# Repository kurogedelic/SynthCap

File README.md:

# SynthCap

A MIDI / CV interface "Cap" for the M5Stack CardputerZero. It plugs into the EXT 2.54-14P header. Designed in KiCad 10.

| Front (encoders) | Back (jacks and SMD parts) |
|---|---|
|  |  |

**Status: work in progress.** The board has been auto-routed but never built. Nothing here is tested on hardware.

## Features
- MCU: CH32V303CBT6, connected to the CardputerZero as a USB MIDI device (EXT pins 1 and 3)
- MIDI IN / OUT on 3.5mm TRS (Type A)
- 2 x CV out (0-5V, internal DAC + LMV324) and 2 x Gate out
- Clock in / out
- 4 x rotary encoder with push switch (Alps EC12E)
- 80 x 32mm, 2 layers. All SMD parts are on the back, for single-side assembly at JLCPCB
- Firmware upload is meant to work from the CardputerZero alone, over the chip's USB ISP bootloader (`wchisp`)

## Schematic
[Schematic (PDF)](docs/schematic.pdf)

## Folders
| Path | Contents |
|---|---|
| `SynthCap.kicad_*` | KiCad project |
| `SynthCap.pretty/`, `SynthCap.3dshapes/` | Project footprints and 3D models |
| `tools/` | Scripts that generate the schematic, footprints and board. `tools/design.py` is the single source for the circuit |
| `jlcpcb/` | BOM and CPL for JLCPCB assembly |
| `shell/` | 3D-printed shell (OpenSCAD) |
| `docs/` | Schematic and renders |
| `memos/` | Design notes (Japanese) |

## Not included
- The PJ-342 jack datasheet (LCSC part C668606). The footprint was drawn from its land pattern drawing.
- The Alps EC11E STEP model. To see the encoders in the 3D viewer, put `EC11E-05SW.STEP` in `SynthCap.3dshapes/`.

## Known open points
- The Tip / Ring pin mapping of the PJ-342 jack is read from the drawing and not confirmed on a real part.
- The encoder footprint uses SMD pads for a through-hole part (legs are bent or cut and soldered on the surface).
- The position of the mounting ear holes against the CardputerZero screw points is estimated from drawings.

## Warning
`tools/gen_pcb.py` rebuilds the board from scratch and removes all routing. Do not run it on a routed board.

## License
Copyright (c) 2026 kurogedelic

- Hardware design, shell and documentation (everything outside `tools/`): [CC BY-SA 4.0](LICENSE)
- Scripts in `tools/`: [MIT](tools/LICENSE)

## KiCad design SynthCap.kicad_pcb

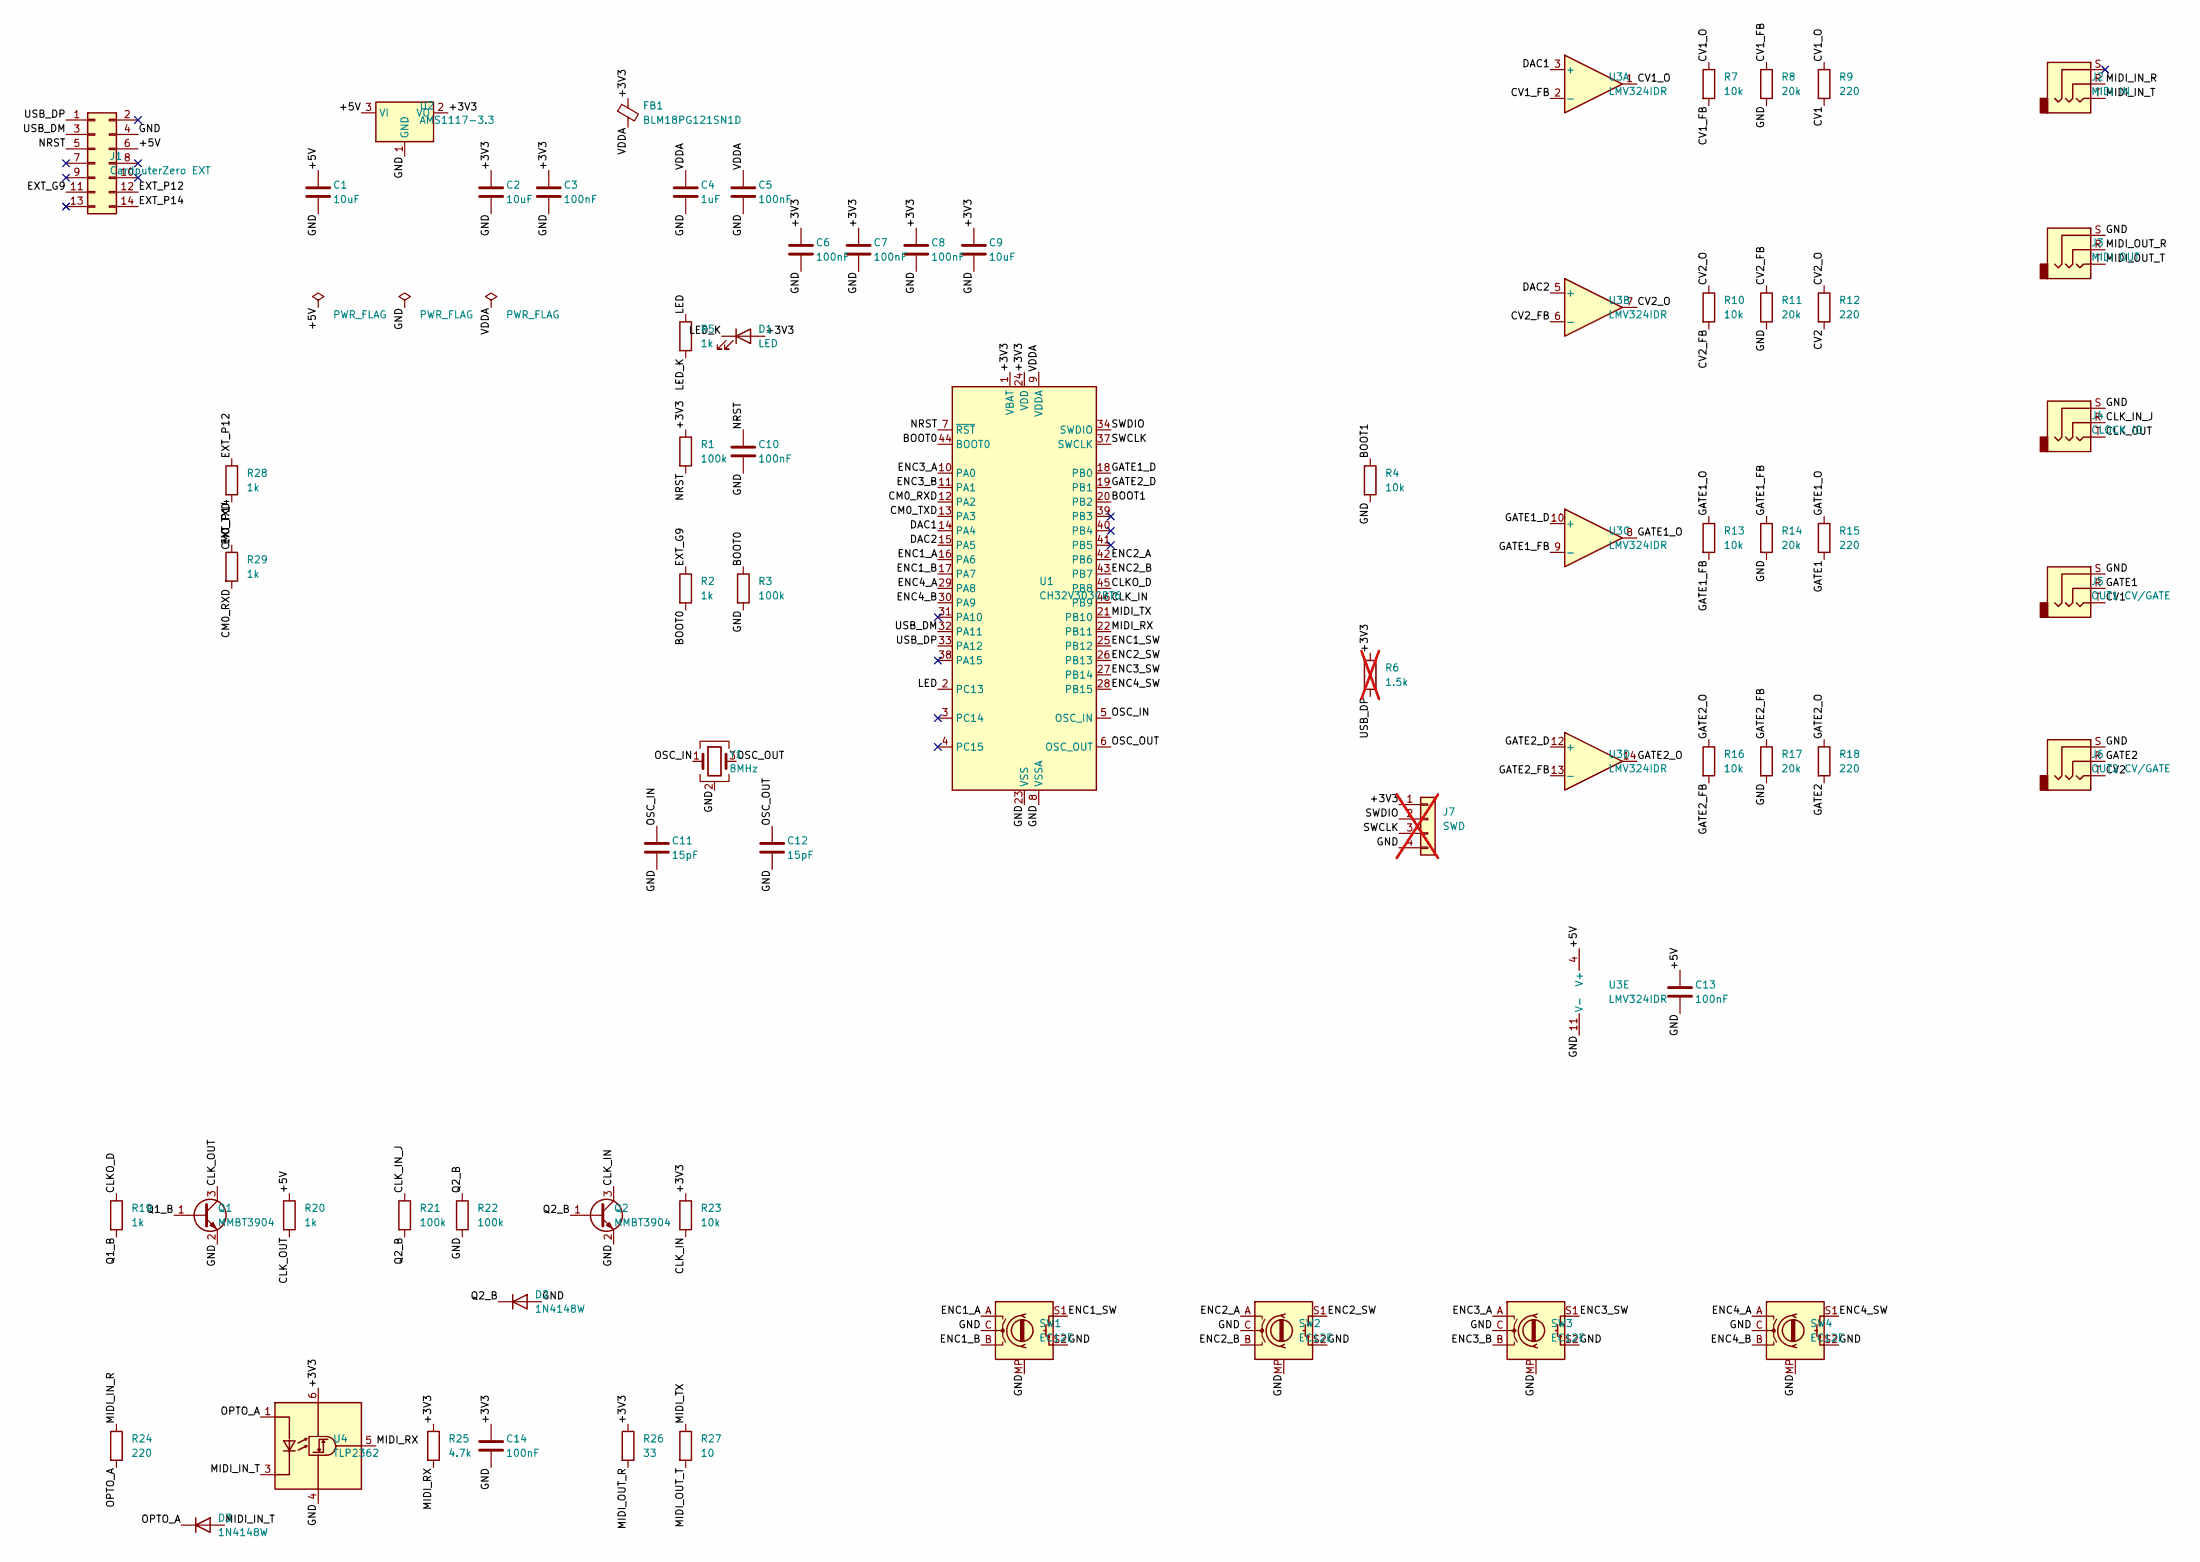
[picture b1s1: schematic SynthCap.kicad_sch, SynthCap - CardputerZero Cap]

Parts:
C1, C2, C9: 10uF; C_0805_2012Metric; LCSC C15850
C3, C5, C6, C7, C8, C10, C13, C14: 100nF; C_0603_1608Metric; LCSC C14663
C4: 1uF; C_0603_1608Metric; LCSC C15849
C11, C12: 15pF; C_0603_1608Metric; LCSC C1644
D1: LED; LED_0603_1608Metric; LCSC C2286
D2, D3: 1N4148W; D_SOD-123; LCSC C81598
FB1: BLM18PG121SN1D; L_0603_1608Metric; LCSC C14709
J1: CardputerZero EXT; PinHeader_2x07_P2.54mm_Horizontal
J2: MIDI IN; Jack_3.5mm_SHOUHAN_PJ-342_SMD; LCSC C668606
J3: MIDI OUT; Jack_3.5mm_SHOUHAN_PJ-342_SMD; LCSC C668606
J4: CLOCK IO; Jack_3.5mm_SHOUHAN_PJ-342_SMD; LCSC C668606
J5: OUT1 CV/GATE; Jack_3.5mm_SHOUHAN_PJ-342_SMD; LCSC C668606
J6: OUT2 CV/GATE; Jack_3.5mm_SHOUHAN_PJ-342_SMD; LCSC C668606
J7: SWD; PinHeader_1x04_P1.27mm_Vertical; not fitted
Q1, Q2: MMBT3904; SOT-23; LCSC C20526
R1, R3, R21, R22: 100k; R_0603_1608Metric; LCSC C25803
R2, R5, R19, R20, R28, R29: 1k; R_0603_1608Metric; LCSC C21190
R4, R7, R10, R13, R16, R23: 10k; R_0603_1608Metric; LCSC C25804
R6: 1.5k; R_0603_1608Metric; LCSC C22843; not fitted
R8, R11, R14, R17: 20k; R_0603_1608Metric; LCSC C4184
R9, R12, R15, R18, R24: 220; R_0603_1608Metric; LCSC C22962
R25: 4.7k; R_0603_1608Metric; LCSC C23162
R26: 33; R_0603_1608Metric; LCSC C23140
R27: 10; R_0603_1608Metric; LCSC C22859
SW1, SW2, SW3, SW4: EC12E; RotaryEncoder_Alps_EC12E-Switch_Vertical_H20mm_SMDpads
U1: CH32V303CBT6; LQFP-48_7x7mm_P0.5mm; LCSC C7494374
U2: AMS1117-3.3; SOT-223-3_TabPin2; LCSC C6186
U3: LMV324IDR; SOIC-14_3.9x8.7mm_P1.27mm; LCSC C7974
U4: TLP2362; SO-5-6_4.55x3.7mm_P1.27mm; LCSC C37658
Y1: 8MHz; Crystal_SMD_3225-4Pin_3.2x2.5mm; LCSC C367183

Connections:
/+3V3: C2.1, C3.1, C6.1, C7.1, C8.1, C9.1, C14.1, D1.2 (A), FB1.1, J7.1, R1.1, R6.1, R23.1, R25.1, R26.1, U1.1 (VBAT), U1.24 (VDD), U1.36 (VDD), U1.48 (VDD), U2.2 (VO), U4.6 (VDD)
/+5V: C1.1, C13.1, J1.6, R20.1, U2.3 (VI), U3.4 (V+)
/BOOT0: R2.2, R3.1, U1.44 (BOOT0)
/BOOT1: R4.1, U1.20 (PB2)
/CLKO_D: R19.1, U1.45 (PB8)
/CLK_IN: Q2.3 (C), R23.2, U1.46 (PB9)
/CLK_IN_J: J4.R, R21.1
/CLK_OUT: J4.T, Q1.3 (C), R20.2
/CM0_RXD: R29.2, U1.12 (PA2)
/CM0_TXD: R28.2, U1.13 (PA3)
/CV1: J5.T, R9.2
/CV1_FB: R7.2, R8.1, U3.2 (-)
/CV1_O: R7.1, R9.1, U3.1
/CV2: J6.T, R12.2
/CV2_FB: R10.2, R11.1, U3.6 (-)
/CV2_O: R10.1, R12.1, U3.7
/DAC1: U1.14 (PA4), U3.3 (+)
/DAC2: U1.15 (PA5), U3.5 (+)
/ENC1_A: SW1.A, U1.16 (PA6)
/ENC1_B: SW1.B, U1.17 (PA7)
/ENC1_SW: SW1.S1, U1.25 (PB12)
/ENC2_A: SW2.A, U1.42 (PB6)
/ENC2_B: SW2.B, U1.43 (PB7)
/ENC2_SW: SW2.S1, U1.26 (PB13)
/ENC3_A: SW3.A, U1.10 (PA0)
/ENC3_B: SW3.B, U1.11 (PA1)
/ENC3_SW: SW3.S1, U1.27 (PB14)
/ENC4_A: SW4.A, U1.29 (PA8)
/ENC4_B: SW4.B, U1.30 (PA9)
/ENC4_SW: SW4.S1, U1.28 (PB15)
/EXT_G9: J1.11, R2.1
/EXT_P12: J1.12, R28.1
/EXT_P14: J1.14, R29.1
/GATE1: J5.R, R15.2
/GATE1_D: U1.18 (PB0), U3.10 (+)
/GATE1_FB: R13.2, R14.1, U3.9 (-)
/GATE1_O: R13.1, R15.1, U3.8
/GATE2: J6.R, R18.2
/GATE2_D: U1.19 (PB1), U3.12 (+)
/GATE2_FB: R16.2, R17.1, U3.13 (-)
/GATE2_O: R16.1, R18.1, U3.14
/GND: C1.2, C2.2, C3.2, C4.2, C5.2, C6.2, C7.2, C8.2, C9.2, C10.2, C11.2, C12.2, C13.2, C14.2, D2.2 (A), J1.4, J3.S, J4.S, J5.S, J6.S, J7.4, Q1.2 (E), Q2.2 (E), R3.2, R4.2, R8.2, R11.2, R14.2, R17.2, R22.2, SW1.C, SW1.MP, SW1.S2, SW2.C, SW2.MP, SW2.S2, SW3.C, SW3.MP, SW3.S2, SW4.C, SW4.MP, SW4.S2, U1.8 (VSSA), U1.23 (VSS), U1.35 (VSS), U1.47 (VSS), U2.1 (GND), U3.11 (V-), U4.4 (GND), Y1.2 (G), Y1.4 (G)
/LED: R5.1, U1.2 (PC13)
/LED_K: D1.1 (K), R5.2
/MIDI_IN_R: J2.R, R24.1
/MIDI_IN_T: D3.2 (A), J2.T, U4.3 (K)
/MIDI_OUT_R: J3.R, R26.2
/MIDI_OUT_T: J3.T, R27.2
/MIDI_RX: R25.2, U1.22 (PB11), U4.5 (VO)
/MIDI_TX: R27.1, U1.21 (PB10)
/NRST: C10.1, J1.5, R1.2, U1.7 (~RST)
/OPTO_A: D3.1 (K), R24.2, U4.1 (A)
/OSC_IN: C11.1, U1.5 (OSC_IN), Y1.1
/OSC_OUT: C12.1, U1.6 (OSC_OUT), Y1.3
/Q1_B: Q1.1 (B), R19.2
/Q2_B: D2.1 (K), Q2.1 (B), R21.2, R22.1
/SWCLK: J7.3, U1.37 (SWCLK)
/SWDIO: J7.2, U1.34 (SWDIO)
/USB_DM: J1.3, U1.32 (PA11)
/USB_DP: J1.1, R6.2, U1.33 (PA12)
/VDDA: C4.1, C5.1, FB1.2, U1.9 (VDDA)

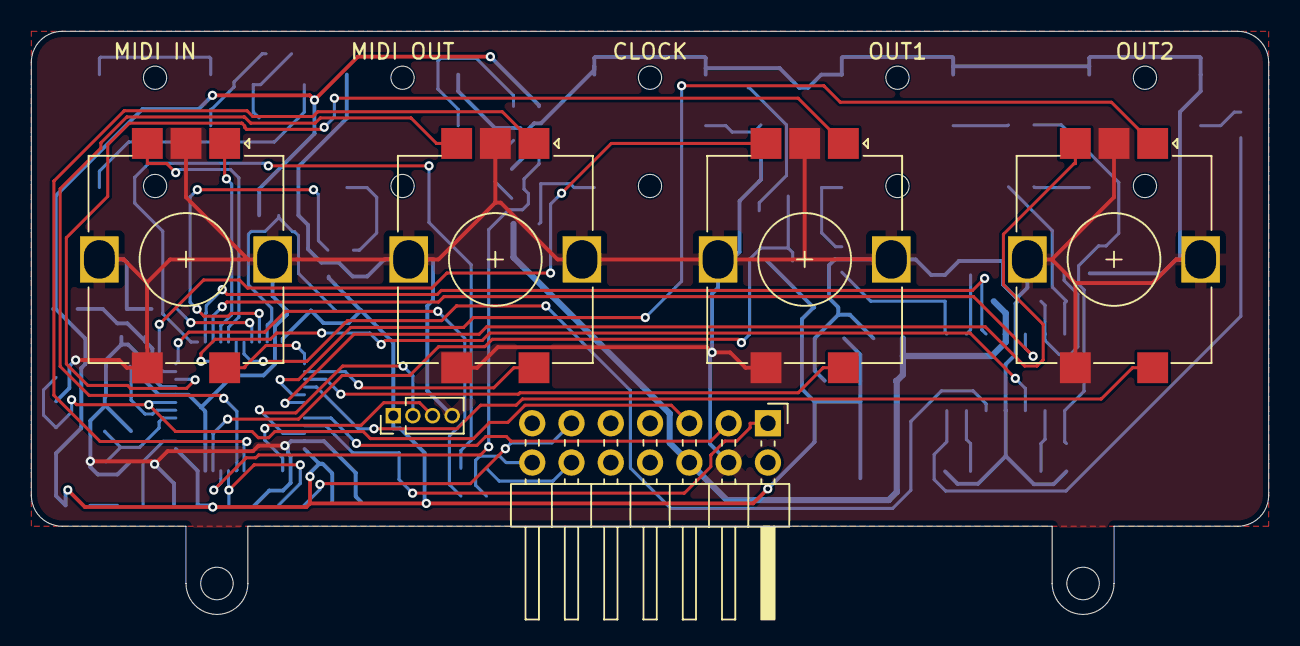
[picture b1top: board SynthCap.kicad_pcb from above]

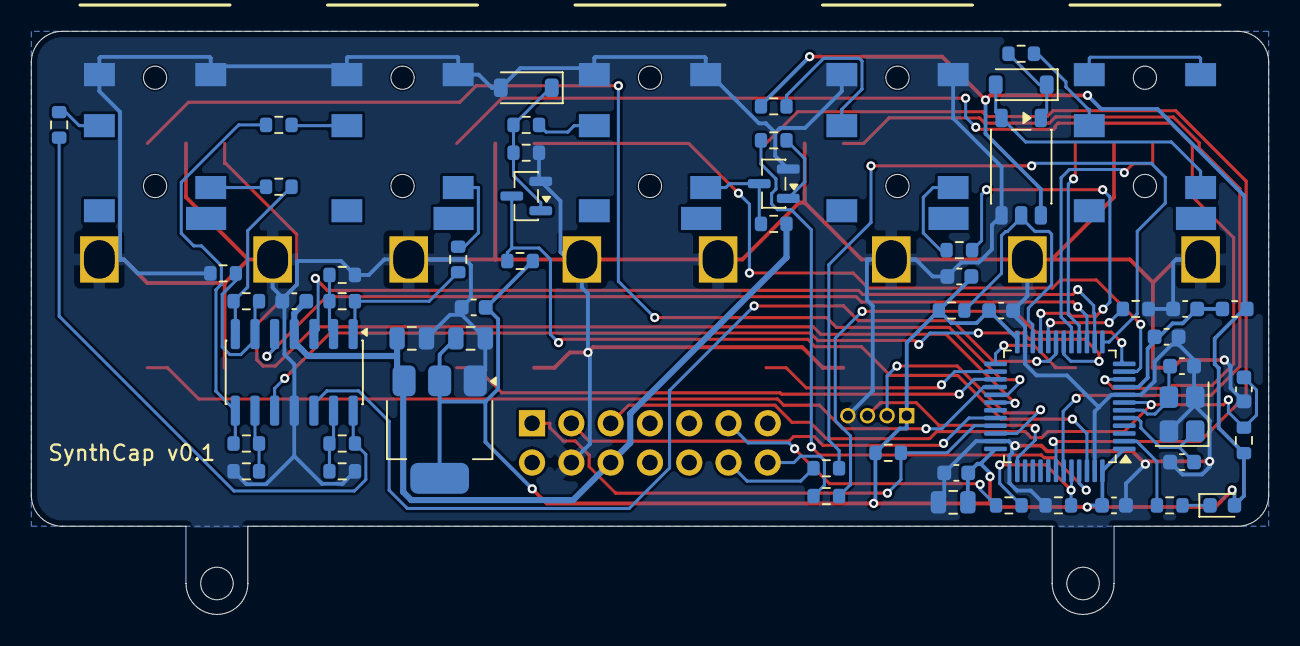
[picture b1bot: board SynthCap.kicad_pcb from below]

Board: 2 copper layers, 80.0 x 37.7 mm, 65 parts (59 on the bottom side), 61 nets.

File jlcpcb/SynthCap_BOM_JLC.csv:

Comment,Designator,Footprint,LCSC Part #
10uF,"C1,C2,C9",C_0805_2012Metric,C15850
100nF,"C3,C5,C6,C7,C8,C10,C13,C14",C_0603_1608Metric,C14663
1uF,C4,C_0603_1608Metric,C15849
15pF,"C11,C12",C_0603_1608Metric,C1644
LED,D1,LED_0603_1608Metric,C2286
1N4148W,"D2,D3",D_SOD-123,C81598
BLM18PG121SN1D,FB1,L_0603_1608Metric,C14709
MIDI IN,J2,Jack_3.5mm_SHOUHAN_PJ-342_SMD,C668606
MIDI OUT,J3,Jack_3.5mm_SHOUHAN_PJ-342_SMD,C668606
CLOCK IO,J4,Jack_3.5mm_SHOUHAN_PJ-342_SMD,C668606
OUT1 CV/GATE,J5,Jack_3.5mm_SHOUHAN_PJ-342_SMD,C668606
OUT2 CV/GATE,J6,Jack_3.5mm_SHOUHAN_PJ-342_SMD,C668606
MMBT3904,"Q1,Q2",SOT-23,C20526
100k,"R1,R3,R21,R22",R_0603_1608Metric,C25803
1k,"R2,R5,R19,R20,R28,R29",R_0603_1608Metric,C21190
10k,"R4,R7,R10,R13,R16,R23",R_0603_1608Metric,C25804
20k,"R8,R11,R14,R17",R_0603_1608Metric,C4184
220,"R9,R12,R15,R18,R24",R_0603_1608Metric,C22962
4.7k,R25,R_0603_1608Metric,C23162
33,R26,R_0603_1608Metric,C23140
10,R27,R_0603_1608Metric,C22859
CH32V303CBT6,U1,LQFP-48_7x7mm_P0.5mm,C7494374
AMS1117-3.3,U2,SOT-223-3_TabPin2,C6186
LMV324IDR,U3,SOIC-14_3.9x8.7mm_P1.27mm,C7974
TLP2362,U4,SO-5-6_4.55x3.7mm_P1.27mm,C37658
8MHz,Y1,Crystal_SMD_3225-4Pin_3.2x2.5mm,C367183

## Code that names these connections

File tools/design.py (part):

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    "5": "OSC_IN", "6": "OSC_OUT", "7": "NRST",
    "8": "GND", "9": "VDDA",
    "10": "ENC3_A", "11": "ENC3_B",
    "12": "CM0_RXD",   # PA2 USART2_TX → CM0 UART_RXD(G15)
    "13": "CM0_TXD",   # PA3 USART2_RX ← CM0 UART_TXD(G14)
    "14": "DAC1", "15": "DAC2",
    "16": "ENC1_A", "17": "ENC1_B",
    "18": "GATE1_D", "19": "GATE2_D", "20": "BOOT1",
    "21": "MIDI_TX", "22": "MIDI_RX",  # USART3
    "23": "GND", "24": "+3V3",
    "25": "ENC1_SW", "26": "ENC2_SW", "27": "ENC3_SW", "28": "ENC4_SW",
    "29": "ENC4_A", "30": "ENC4_B",  # PA8/PA9 TIM1
    "31": None,
    "32": "USB_DM", "33": "USB_DP",
    "34": "SWDIO", "35": "GND", "36": "+3V3", "37": "SWCLK",
    "38": None,
    "39": None,  # PB3（未使用）
    "40": None, "41": None,
    "42": "ENC2_A", "43": "ENC2_B",  # PB6/PB7 TIM4
    "44": "BOOT0",
    "45": "CLKO_D", "46": "CLK_IN",  # PB8/PB9
    "47": "GND", "48": "+3V3",
}
add("U1", "MCU_WCH_RiscV:CH32V30xCxTx", "CH32V303CBT6", "Package_QFP:LQFP-48_7x7mm_P0.5mm",
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C("C12", "15pF", "OSC_OUT", "GND", (155, 165))
R("R5", "1k", "LED", "LED_K", (140, 75))
add("D1", "Device:LED", "LED", "LED_SMD:LED_0603_1608Metric", "C2286", (150, 75),
    {"1": "LED_K", "2": "+3V3"})  # PC13がLowで点灯
# USB D+プルアップ（CH32V303は内蔵プルアップあり。念のための未実装パッド）
R("R6", "1.5k", "+3V3", "USB_DP", (260, 135), dnp=True)
# SWD（WCH-LinkE）用パッド。未実装
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# rn == 19

# ---------------------------------------------------------------- Clock 入出力
# 出力: PB8 → NPN → 1kプルアップ(+5V)。ファーム側で論理反転して出す
R("R19", "1k", "CLKO_D", "Q1_B", (40, 230))
add("Q1", "Transistor_BJT:MMBT3904", "MMBT3904", "Package_TO_SOT_SMD:SOT-23", "C20526",
    (55, 230), {"1": "Q1_B", "2": "GND", "3": "CLK_OUT"})
R("R20", "1k", "+5V", "CLK_OUT", (70, 230))
# 入力: 0〜10V、負電圧にも耐える。約1.2Vでスイッチ、PB9には反転して入る
R("R21", "100k", "CLK_IN_J", "Q2_B", (90, 230))
R("R22", "100k", "Q2_B", "GND", (100, 230))
add("D2", "Device:D", "1N4148W", "Diode_SMD:D_SOD-123", "C81598", (110, 245),
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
